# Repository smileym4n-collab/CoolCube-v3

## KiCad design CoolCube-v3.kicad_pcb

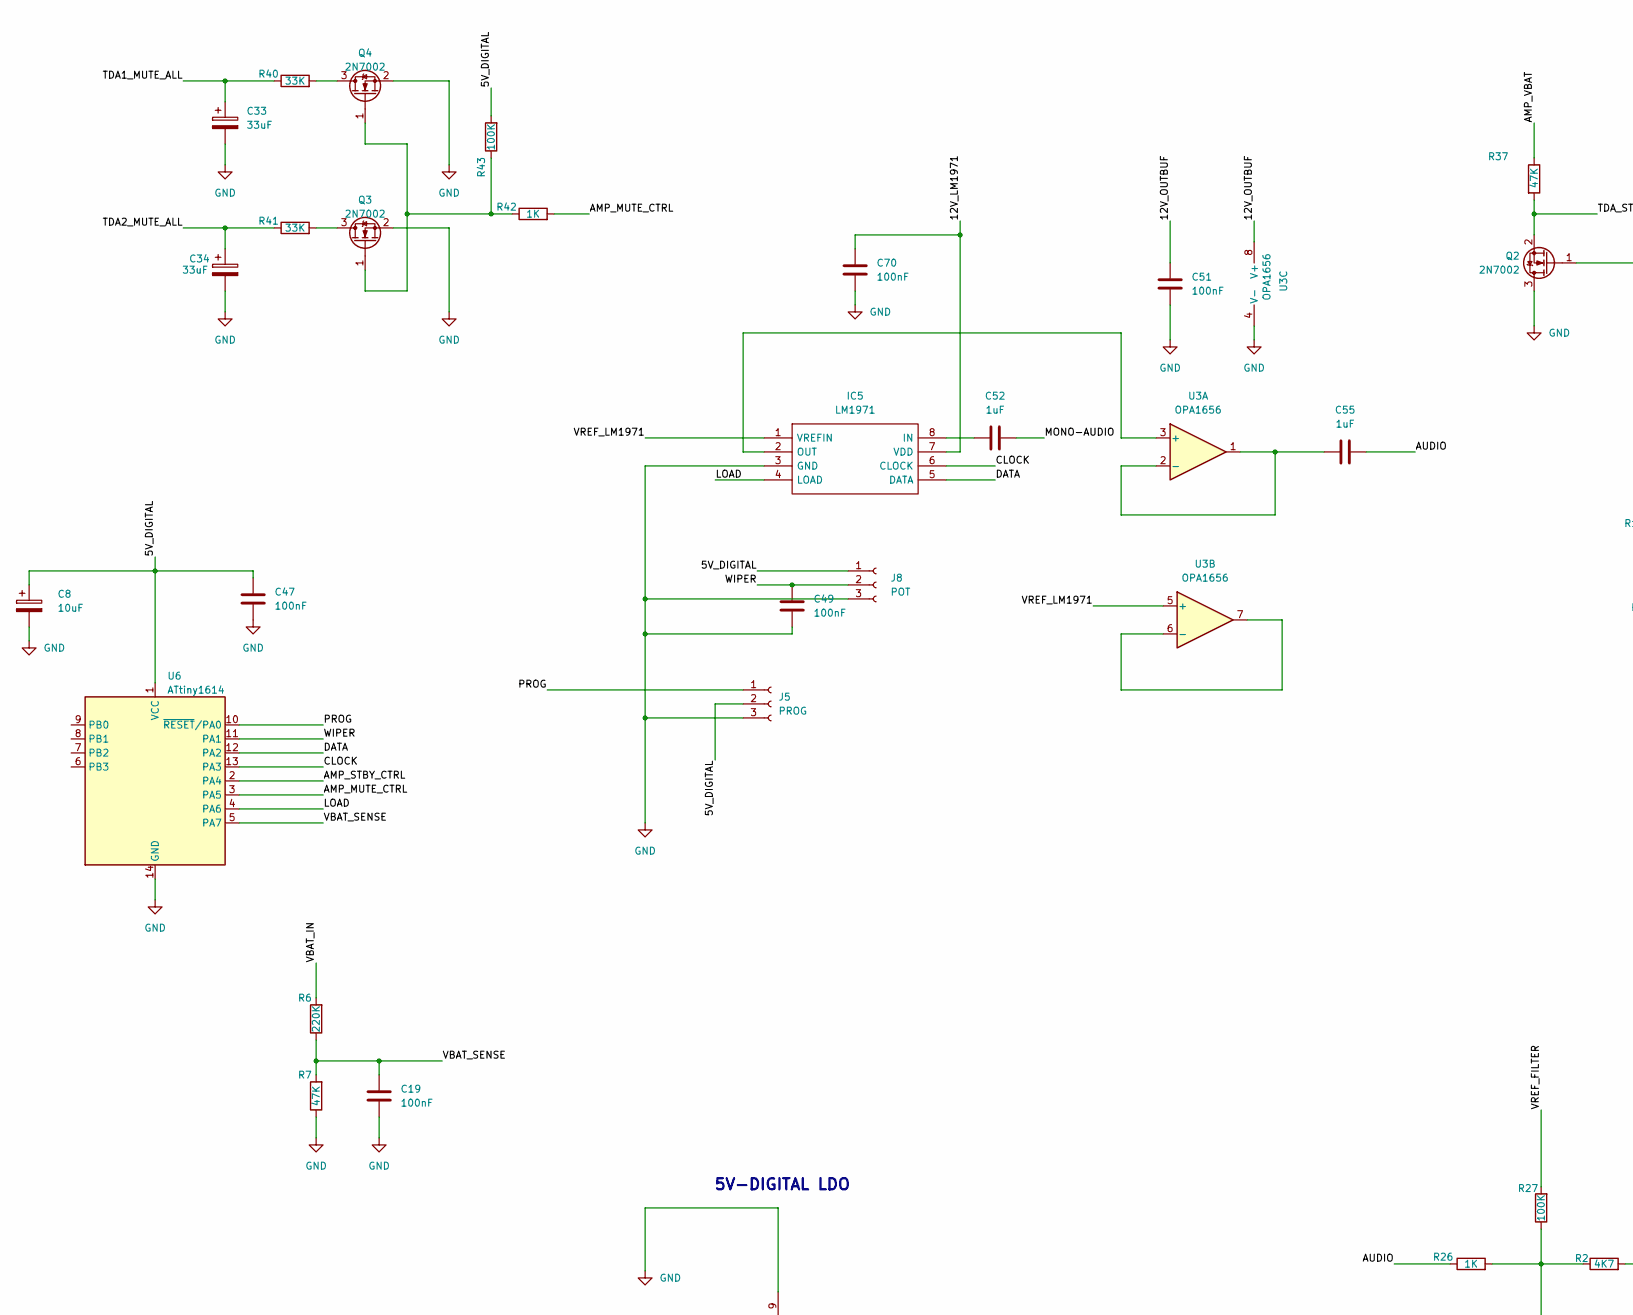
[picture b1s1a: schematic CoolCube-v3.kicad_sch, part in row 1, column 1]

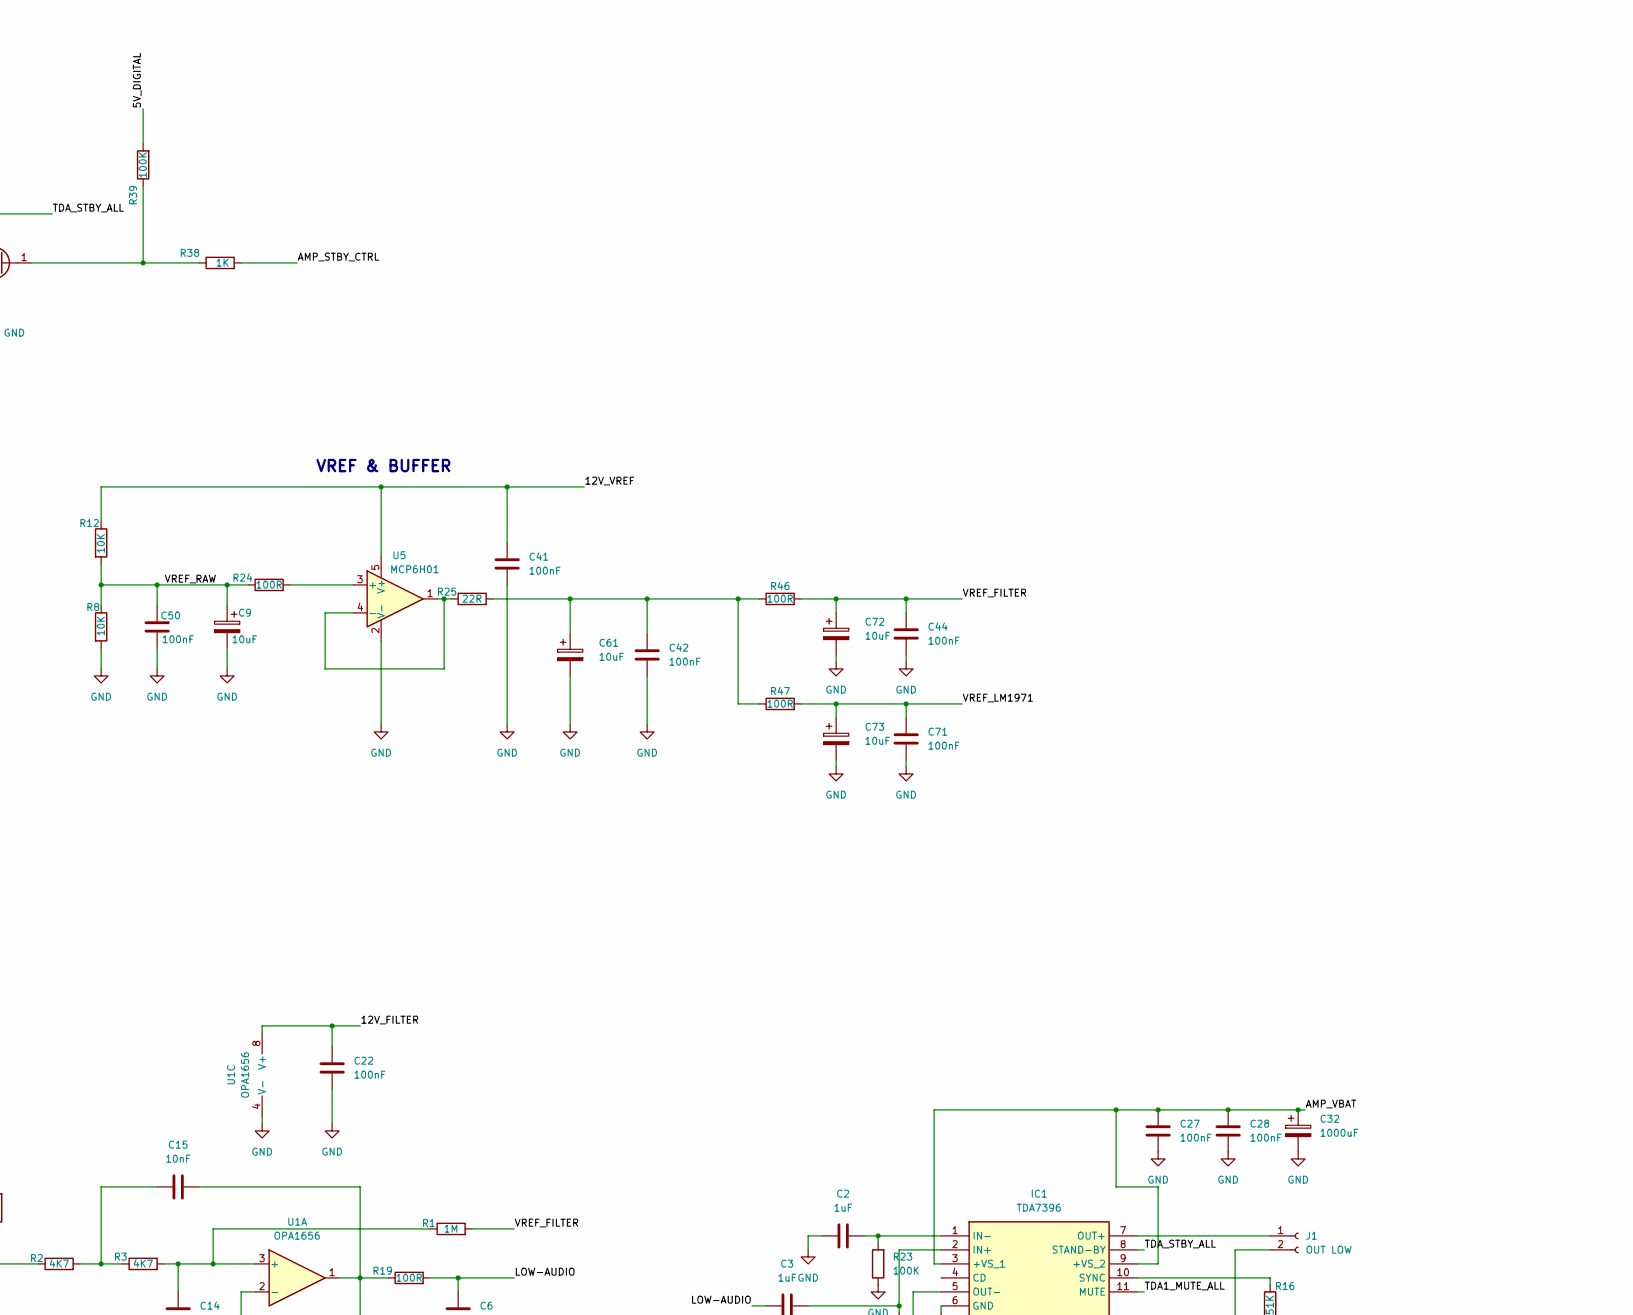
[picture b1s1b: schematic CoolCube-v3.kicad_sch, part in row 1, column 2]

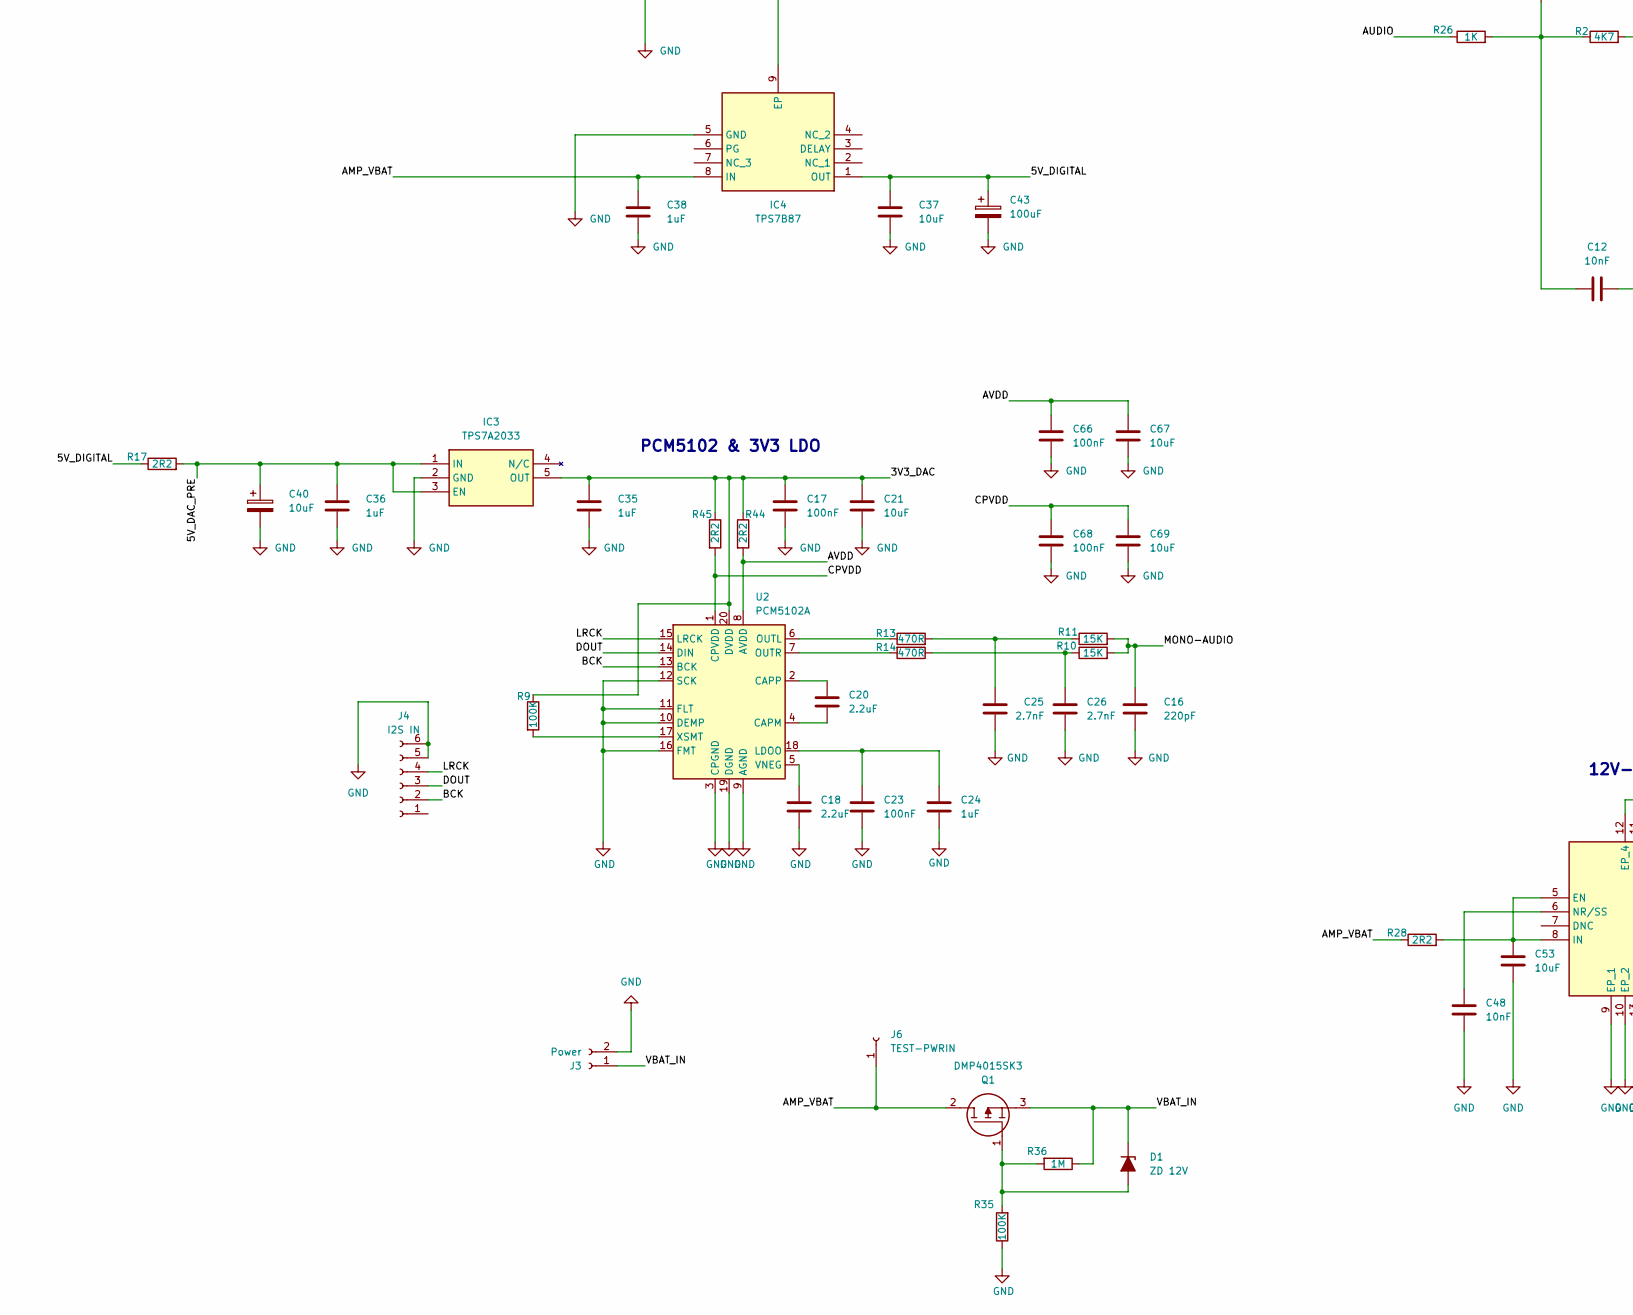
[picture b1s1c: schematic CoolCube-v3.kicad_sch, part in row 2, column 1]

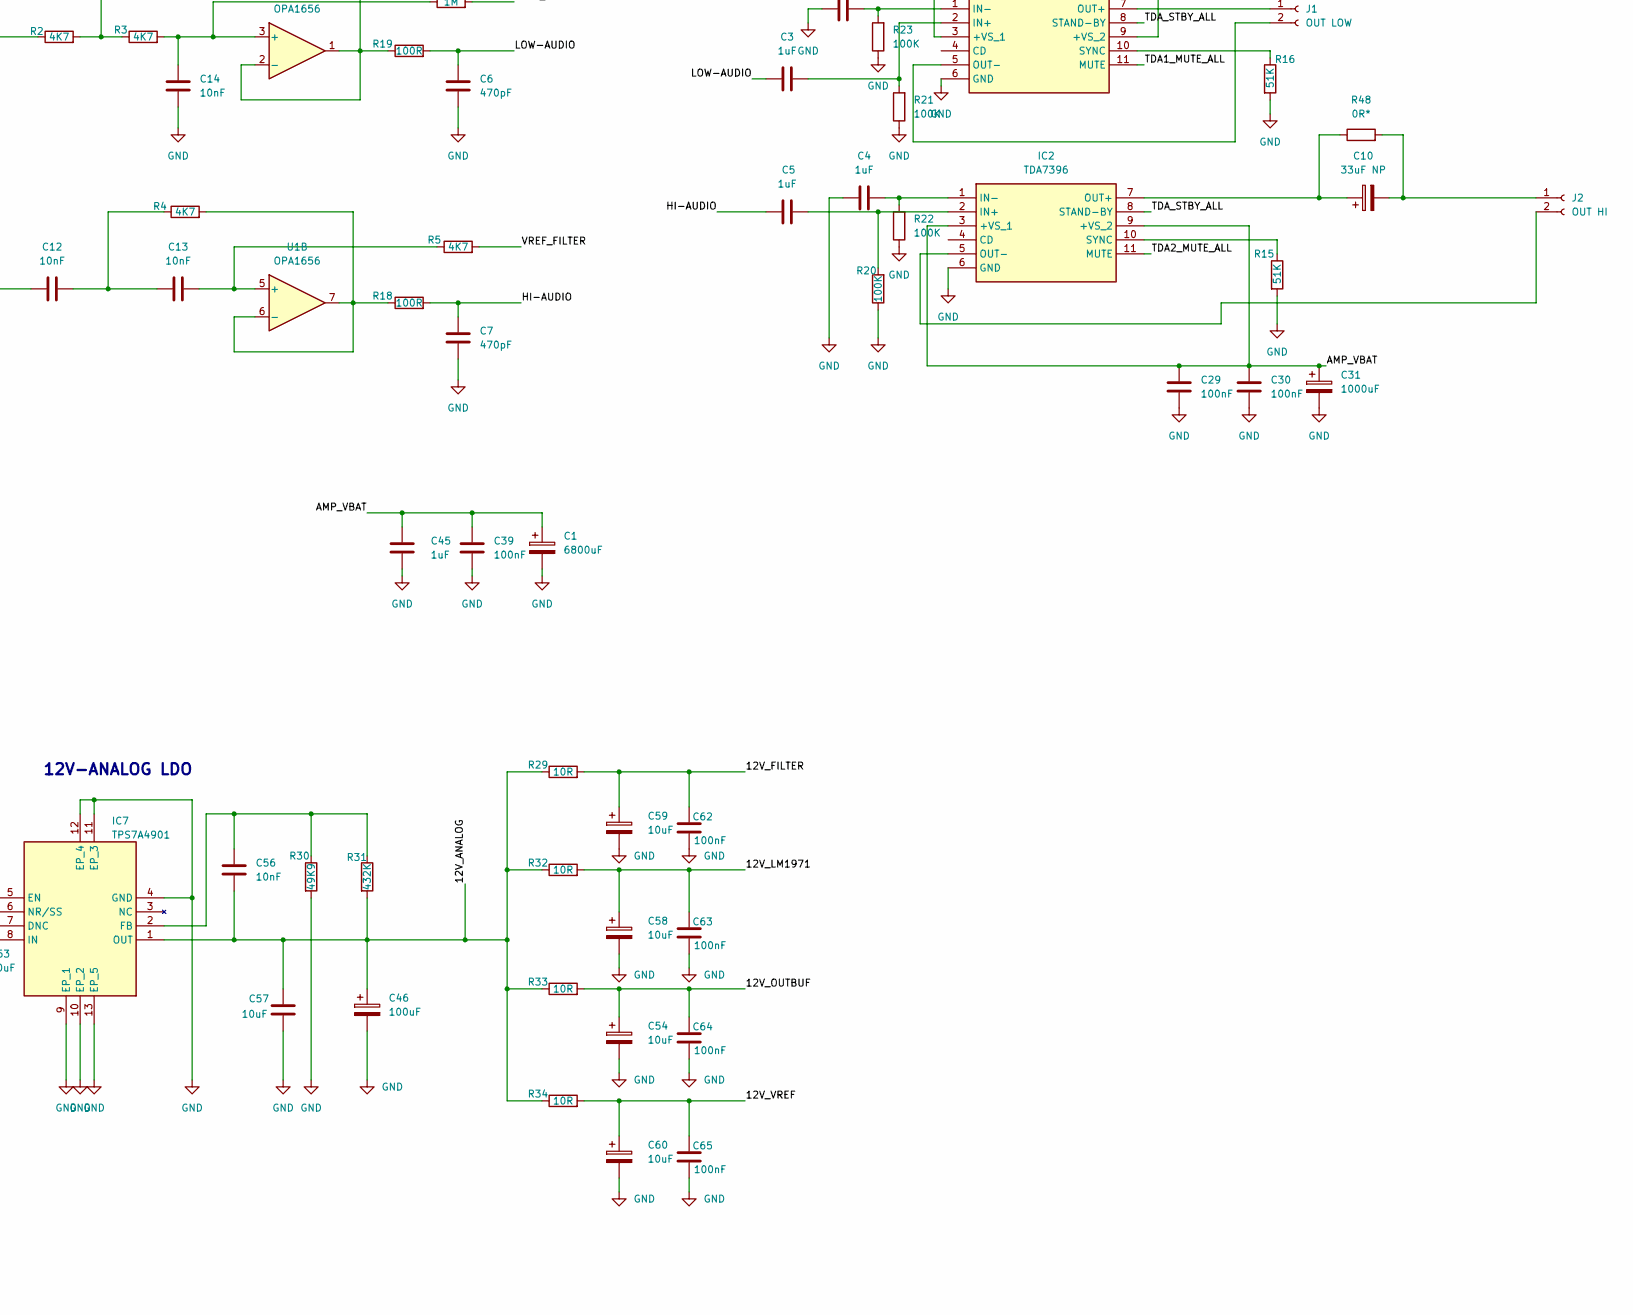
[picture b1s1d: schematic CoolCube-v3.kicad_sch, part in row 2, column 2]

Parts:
C1: 6800uF; CP_Radial_D18.0mm_P7.50mm
C2, C3, C4, C5: 1uF; C_Rect_L7.0mm_W4.5mm_P5.00mm
C6, C7: 470pF; C_0805_2012Metric_Pad1.18x1.45mm_HandSolder
C8, C9, C40, C54, C58, C59, C60, C61, C72, C73: 10uF; CP_Radial_D4.0mm_P1.50mm
C10: 33uF NP; CP_Axial_L26.5mm_D13mm_P33.00mm_Horizontal
C12, C13, C14, C15, C48, C56: 10nF; C_0805_2012Metric_Pad1.18x1.45mm_HandSolder
C16: 220pF; C_0805_2012Metric_Pad1.18x1.45mm_HandSolder
C17, C19, C22, C23, C27, C28, C29, C30, C39, C41, C42, C44, C47, C49, C50, C51, C62, C63, C64, C65, C66, C68, C70, C71: 100nF; C_1206_3216Metric_Pad1.33x1.80mm_HandSolder
C18, C20: 2.2uF; C_0805_2012Metric_Pad1.18x1.45mm_HandSolder
C21, C67, C69: 10uF; C_0805_2012Metric_Pad1.18x1.45mm_HandSolder
C24, C35, C36, C38, C45: 1uF; C_1206_3216Metric_Pad1.33x1.80mm_HandSolder
C25, C26: 2.7nF; C_0805_2012Metric_Pad1.18x1.45mm_HandSolder
C31, C32: 1000uF; CP_Radial_D12.5mm_P5.00mm
C33, C34: 33uF; CP_Radial_D5.0mm_P2.50mm
C37, C53, C57: 10uF; C_1206_3216Metric_Pad1.33x1.80mm_HandSolder
C43, C46: 100uF; CP_Radial_D8.0mm_P3.50mm
C52, C55: 1uF; C_Rect_L7.2mm_W5.5mm_P5.00mm_FKS2_FKP2_MKS2_MKP2
D1: ZD 12V; D_DO-201AD_P12.70mm_Horizontal
IC1, IC2: TDA7396; TDA7391; Mouser Part Number 511-TDA7391
IC3: TPS7A2033; SOT95P280X145-5N; Mouser Part Number 595-TPS7A2033PDBVR
IC4: TPS7B87; TPS7B8750QDDARQ1; Mouser Part Number 595-TPS7B8750QDDARQ1
IC5: LM1971; SOIC-8_3.9x4.9mm_P1.27mm; Mouser Part Number 926-LM1971MX/NOPB
IC7: TPS7A4901; TPS7A4901DRBR; Mouser Part Number 595-TPS7A4901DRBR
J1: OUT LOW; JST_XA_B02B-XASK-1_1x02_P2.50mm_Vertical
J2: OUT HI; JST_XA_B02B-XASK-1_1x02_P2.50mm_Vertical
J3: Power; JST_XA_B02B-XASK-1_1x02_P2.50mm_Vertical
J4: I2S IN; JST_XH_B6B-XH-A_1x06_P2.50mm_Vertical
J5: PROG; PinHeader_1x03_P2.54mm_Vertical
J6: TEST-PWRIN; PinHeader_1x01_P2.54mm_Vertical
J8: POT; JST_XH_B3B-XH-A_1x03_P2.50mm_Vertical
Q1: DMP4015SK3; DMP4015SK313; Manufacturer_Part_Number DMP4015SK3-13
Q2, Q3, Q4: 2N7002; SOT-23
R1, R36: 1M; R_0805_2012Metric_Pad1.20x1.40mm_HandSolder
R2, R3, R4, R5: 4K7; R_0805_2012Metric_Pad1.20x1.40mm_HandSolder
R6: 220K; R_0805_2012Metric_Pad1.20x1.40mm_HandSolder
R7, R37: 47K; R_0805_2012Metric_Pad1.20x1.40mm_HandSolder
R8, R12: 10K; R_0805_2012Metric_Pad1.20x1.40mm_HandSolder
R9, R20, R21, R22, R23, R27, R35, R39, R43: 100K; R_0805_2012Metric_Pad1.20x1.40mm_HandSolder
R10, R11: 15K; R_0805_2012Metric_Pad1.20x1.40mm_HandSolder
R13, R14: 470R; R_0805_2012Metric_Pad1.20x1.40mm_HandSolder
R15, R16: 51K; R_0603_1608Metric_Pad0.98x0.95mm_HandSolder
R17, R28, R44, R45: 2R2; R_0805_2012Metric_Pad1.20x1.40mm_HandSolder
R18, R19, R24, R46, R47: 100R; R_0805_2012Metric_Pad1.20x1.40mm_HandSolder
R25: 22R; R_0805_2012Metric_Pad1.20x1.40mm_HandSolder
R26, R38, R42: 1K; R_0805_2012Metric_Pad1.20x1.40mm_HandSolder
R29, R32, R33, R34: 10R; R_0805_2012Metric_Pad1.20x1.40mm_HandSolder
R30: 49K9; R_0805_2012Metric_Pad1.20x1.40mm_HandSolder
R31: 432K; R_0805_2012Metric_Pad1.20x1.40mm_HandSolder
R40, R41: 33K; R_0805_2012Metric_Pad1.20x1.40mm_HandSolder
R48: 0R*; R_0805_2012Metric_Pad1.20x1.40mm_HandSolder
U1, U3: OPA1656; SOIC-8_3.9x4.9mm_P1.27mm
U2: PCM5102A; TSSOP-20_4.4x6.5mm_P0.65mm
U5: MCP6H01; SOT-23-5
U6: ATtiny1614; SOIC-14_3.9x8.7mm_P1.27mm

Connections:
/3V3_DAC: C17.1, C21.1, C35.1, IC3.5 (OUT), R9.1, R44.1, R45.1, U2.20 (DVDD)
/5V_DAC_PRE: C36.1, C40.1, IC3.1 (IN), IC3.3 (EN), R17.2
/5V_DIGITAL: C8.1, C37.1, C43.1, C47.1, IC4.1 (OUT), J5.2, J8.1, R17.1, R39.2, R43.2, U6.1 (VCC)
/12V_ANALOG: C46.1, C56.2, C57.2, IC7.1 (OUT), R29.1, R31.2, R32.1, R33.1, R34.1
/12V_FILTER: C22.1, C59.1, C62.2, R29.2, U1.8 (V+)
/12V_LM1971: C58.1, C63.2, C70.1, IC5.7 (VDD), R32.2
/12V_OUTBUF: C51.1, C54.1, C64.2, R33.2, U3.8 (V+)
/12V_VREF: C41.1, C60.1, C65.2, R12.1, R34.2, U5.5 (V+)
/AMP_MUTE_CTRL: R42.2, U6.3 (PA5)
/AMP_STBY_CTRL: R38.2, U6.2 (PA4)
/AMP_VBAT: C1.1, C27.1, C28.1, C29.1, C30.1, C31.1, C32.1, C38.1, C39.1, C45.1, IC1.3 (+VS_1), IC1.9 (+VS_2), IC2.3 (+VS_1), IC2.9 (+VS_2), IC4.8 (IN), J6.1, Q1.2, R28.1, R37.1
/AUDIO: C55.2, R26.1
/AVDD: C66.1, C67.1, R44.2, U2.8 (AVDD)
/BCK: J4.2, U2.13 (BCK)
/CLOCK: IC5.6 (CLOCK), U6.13 (PA3)
/CPVDD: C68.1, C69.1, R45.2, U2.1 (CPVDD)
/DATA: IC5.5 (DATA), U6.12 (PA2)
/DOUT: J4.3, U2.14 (DIN)
/HI-AUDIO: C5.1, C7.1, R18.2
/LOAD: IC5.4 (LOAD), U6.4 (PA6)
/LOW-AUDIO: C3.1, C6.1, R19.2
/LRCK: J4.4, U2.15 (LRCK)
/MONO-AUDIO: C16.1, C52.2, R10.2, R11.2
/PROG: J5.1, U6.10 (~RESET/PA0)
/TDA1_MUTE_ALL: C33.1, IC1.11 (MUTE), R40.1
/TDA2_MUTE_ALL: C34.1, IC2.11 (MUTE), R41.1
/TDA_STBY_ALL: IC1.8 (STAND-BY), IC2.8 (STAND-BY), Q2.2 (S), R37.2
/VBAT_IN: D1.1 (K), J3.1, Q1.3, R6.2, R36.1
/VBAT_SENSE: C19.1, R6.1, R7.2, U6.5 (PA7)
/VREF_FILTER: C44.1, C72.1, R1.2, R5.2, R27.2, R46.2
/VREF_LM1971: C71.1, C73.1, IC5.1 (VREFIN), R47.2, U3.5 (+)
/VREF_RAW: C9.1, C50.2, R8.1, R12.2, R24.1
/WIPER: C49.1, J8.2, U6.11 (PA1)
GND: C1.2, C2.1, C4.1, C6.2, C7.2, C8.2, C9.2, C14.2, C16.2, C17.2, C18.2, C19.2, C21.2, C22.2, C23.2, C24.2, C25.2, C26.2, C27.2, C28.2, C29.2, C30.2, C31.2, C32.2, C33.2, C34.2, C35.2, C36.2, C37.2, C38.2, C39.2, C40.2, C41.2, C42.2, C43.2, C44.2, C45.2, C46.2, C47.2, C48.2, C49.2, C50.1, C51.2, C53.1, C54.2, C57.1, C58.2, C59.2, C60.2, C61.2, C62.1, C63.1, C64.1, C65.1, C66.2, C67.2, C68.2, C69.2, C70.2, C71.2, C72.2, C73.2, IC1.6 (GND), IC2.6 (GND), IC3.2 (GND), IC4.5 (GND), IC4.9 (EP), IC5.3 (GND), IC7.4 (GND), IC7.9 (EP_1), IC7.10 (EP_2), IC7.11 (EP_3), IC7.12 (EP_4), IC7.13 (EP_5), J3.2, J4.5, J4.6, J5.3, J8.3, Q2.3 (D), Q3.2 (S), Q4.2 (S), R7.1, R8.2, R15.2, R16.2, R20.1, R21.1, R22.1, R23.1, R30.2, R35.1, U1.4 (V-), U2.3 (CPGND), U2.9 (AGND), U2.10 (DEMP), U2.11 (FLT), U2.12 (SCK), U2.16 (FMT), U2.19 (DGND), U3.4 (V-), U5.2 (V-), U6.14 (GND)
unnamed: C12.1, R2.1, R26.2, R27.1
unnamed: C12.2, C13.1, R4.1
unnamed: C15.1, R2.2, R3.1
unnamed: C25.1, R11.1, R13.2
unnamed: C26.1, R10.1, R14.1
unnamed: C42.1, C61.1, R25.2, R46.1, R47.1
unnamed: D1.2 (A), Q1.1, R35.2, R36.2
unnamed: C3.2, IC1.2 (IN+), R21.2
unnamed: C2.2, IC1.1 (IN-), R23.2
unnamed: IC1.7 (OUT+), J1.1
unnamed: IC1.5 (OUT-), J1.2
unnamed: IC1.10 (SYNC), R16.1
unnamed: C5.2, IC2.2 (IN+), R20.2
unnamed: C4.2, IC2.1 (IN-), R22.2
unnamed: C10.1, IC2.7 (OUT+), R48.1
unnamed: IC2.5 (OUT-), J2.2
unnamed: IC2.10 (SYNC), R15.1
unnamed: C52.1, IC5.8 (IN)
unnamed: IC5.2 (OUT), U3.3 (+)
unnamed: C53.2, IC7.5 (EN), IC7.8 (IN), R28.2
unnamed: C56.1, IC7.2 (FB), R30.1, R31.1
unnamed: C48.1, IC7.6 (NR/SS)
unnamed: C10.2, J2.1, R48.2
unnamed: Q2.1 (G), R38.1, R39.1
unnamed: Q3.3 (D), R41.2
unnamed: Q3.1 (G), Q4.1 (G), R42.1, R43.1
unnamed: Q4.3 (D), R40.2
unnamed: C14.1, R1.1, R3.2, U1.3 (+)
unnamed: C15.2, R19.1, U1.1, U1.2 (-)
unnamed: C13.2, R5.1, U1.5 (+)
unnamed: R4.2, R18.1, U1.6 (-), U1.7
unnamed: C20.2, U2.4 (CAPM)
unnamed: C20.1, U2.2 (CAPP)
unnamed: C23.1, C24.1, U2.18 (LDOO)
unnamed: R13.1, U2.6 (OUTL)
unnamed: R14.2, U2.7 (OUTR)
unnamed: C18.1, U2.5 (VNEG)
unnamed: R9.2, U2.17 (XSMT)
unnamed: C55.1, U3.1, U3.2 (-)
unnamed: U3.6 (-), U3.7
unnamed: R24.2, U5.3 (+)
unnamed: R25.1, U5.1, U5.4 (-)

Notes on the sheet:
12V-ANALOG LDO
PCM5102 & 3V3 LDO
VREF & BUFFER
5V-DIGITAL LDO

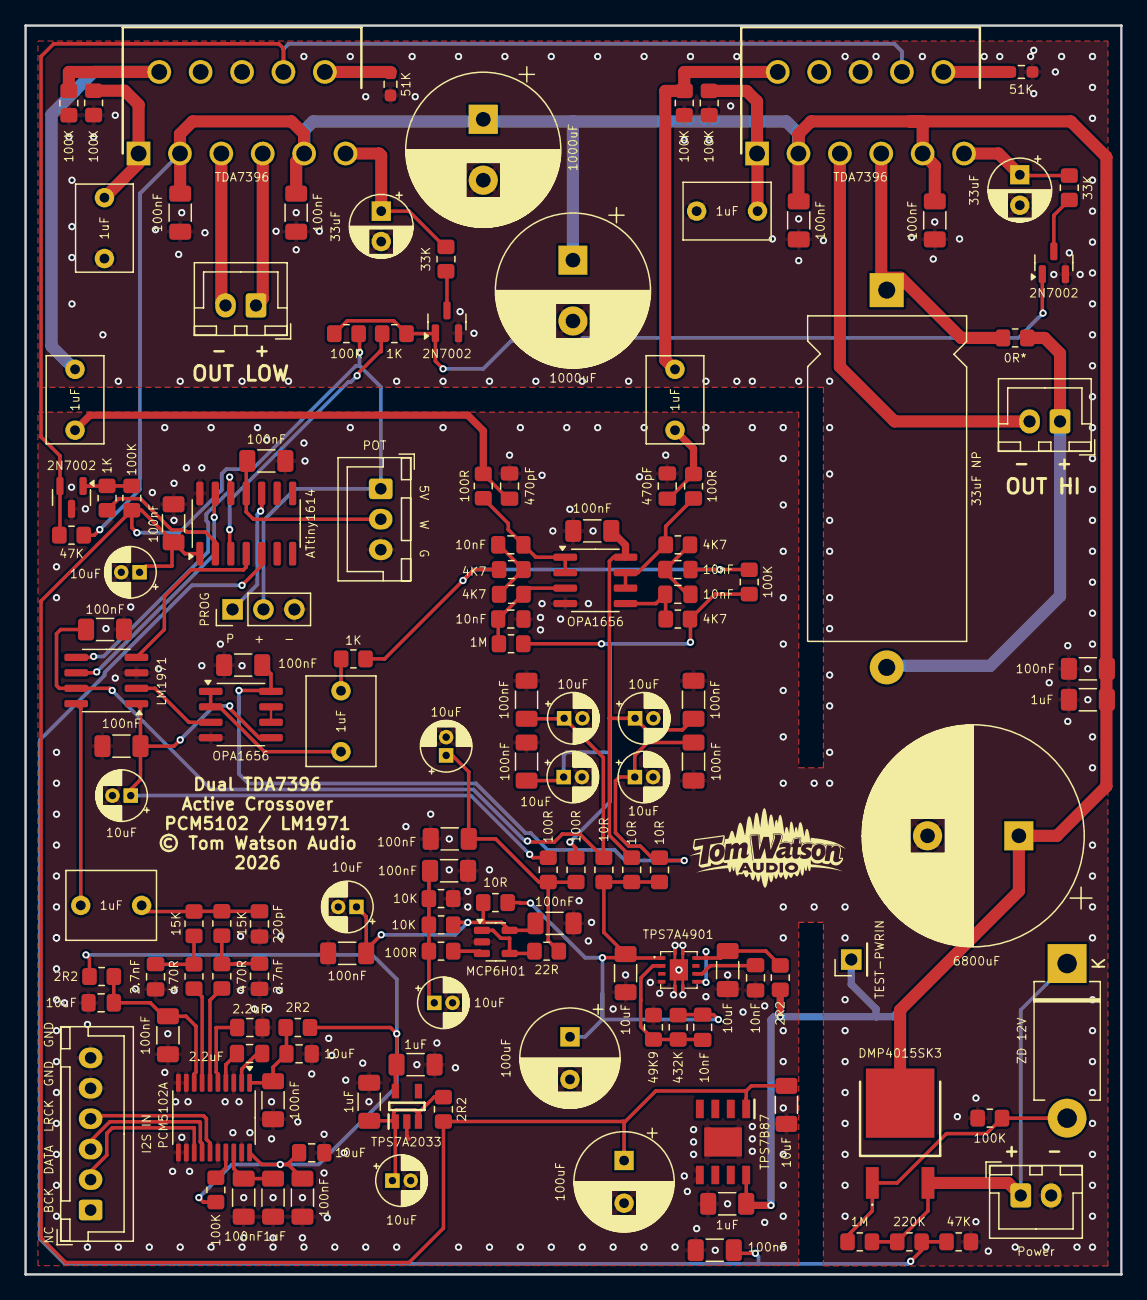
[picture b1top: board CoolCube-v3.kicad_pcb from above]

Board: 2 copper layers, 90.0 x 102.6 mm, 143 parts (0 on the bottom side), 76 nets.

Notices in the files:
CoolCube-v3.kicad_pcb:
© Tom Watson Audio
